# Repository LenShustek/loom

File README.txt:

eLoom: an automation system for the Glimakra "Julia" floor loom 

Tying up a loom with treadles and lamms is complicated, and so is the weaving. 
So I have replaced all the treadles and lamms in our Glimakra "Julia" 
countermarche floor loom with stepper motors that independently operate up to 
8 shafts. That not only makes setup and weaving easier, but it also allows 
patterns that would otherwise not be possible. 

The tie-ups and treadle sequences for up to 16 simulated treadles are 
graphically configured on a small screen. You then weave by throwing the 
shuttle and just pushing the single foot pedal to get the next configuration 
of the shafts. The warping, though, must still be done manually! 

For a one-minute video of it in action, see https://www.youtube.com/watch?v=ygZEDzQJMSk

The hardware added to the loom consists of:
 - up to 8 stepper motors, 23HS22-1504S, NEMA 23, 5.4V, 1.5A, 164 oz-in holding torque
 - up to 8 DRV8825 stepper motor drivers (Pololu or equiv.)
 - a 24VDC 200W power supply
 - 25-pitch sprockets and roller chain to connect the motors to the shaft lines
 - a control box that contains:
   - 1 4-row x 20-character LCD display (Adafruit 198)
   - 1 4-digit 7-segment I2C big digit numerical display (Adafruit 1268)
   - 2 rotary encoders with RGB LEDs and pushbuttons (Sparkfun COM-10982 and BOB-11722)
   - 4 general-purpose pushbuttons (MPJA 32730 or equiv.)
   - 1 attached foot pedal (MPJA 18150 or equiv.)
   - 1 Teensy 3.5 microprocessor, with 512KB flash, 192KB RAM, 4KB EEPROM, and 40 I/O pins
   
Len Shustek, January 2017

October 2020 update: After yeoman service for 3+ years, the plug-in breadboards with the
motor drivers started failing because the high current had deteriorated the contacts.
So I designed a proper printed circuit board replacement that is working great.
The design is in the motordriver subdirectory of this repository.

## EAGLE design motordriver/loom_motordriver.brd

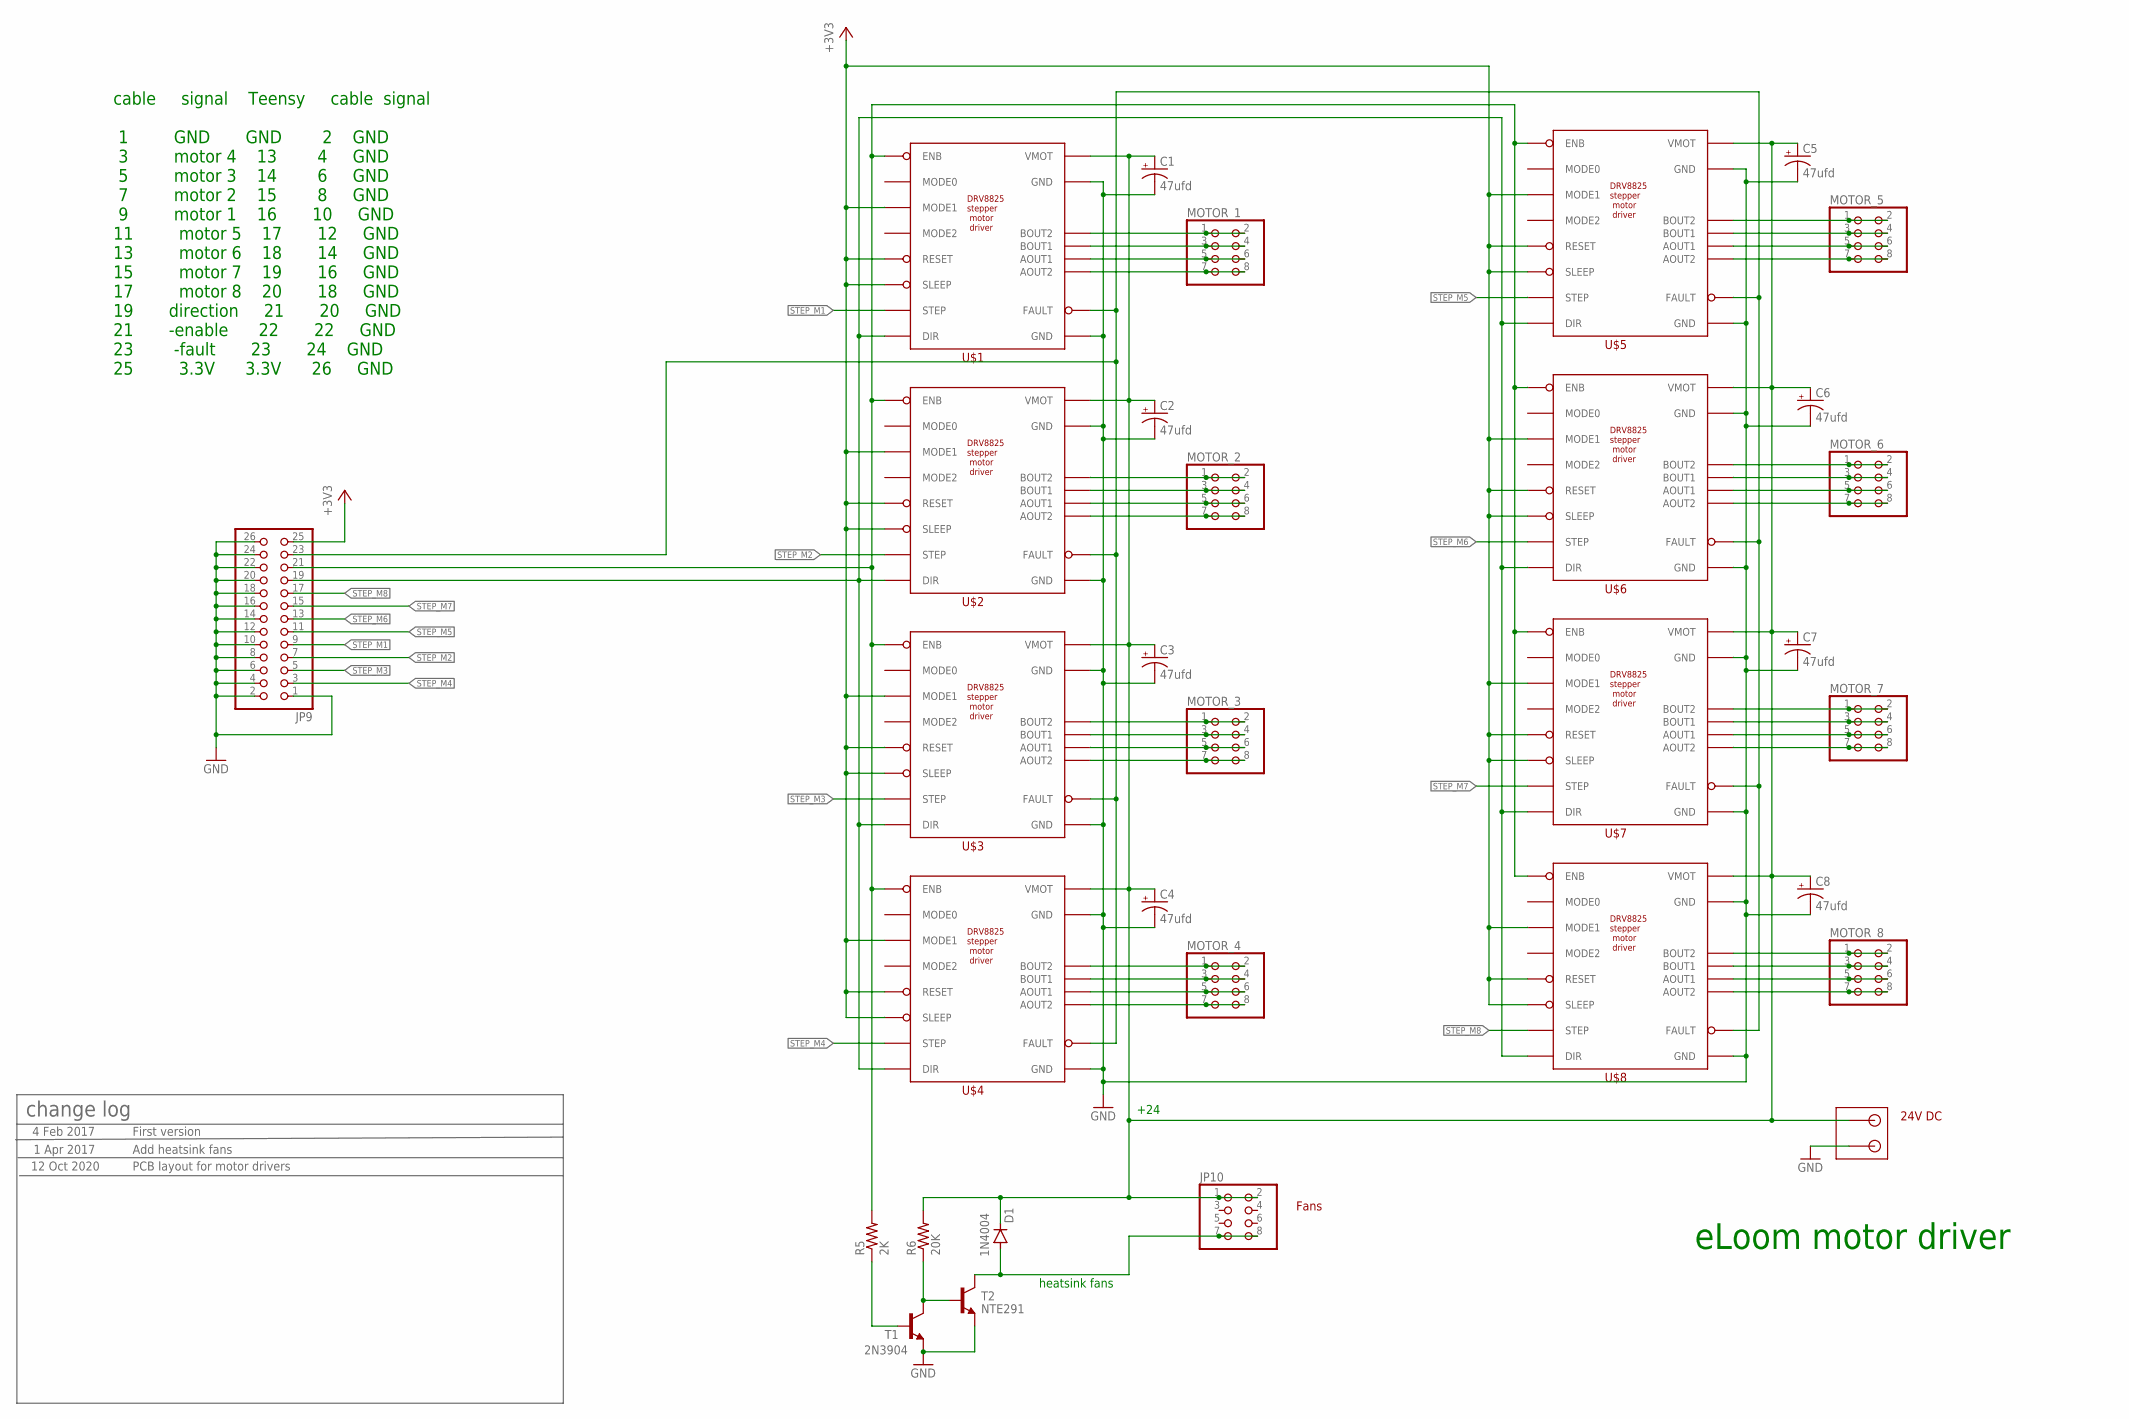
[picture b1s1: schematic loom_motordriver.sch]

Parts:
C1, C2, C3, C4, C5, C6, C7, C8: 47ufd; E2,5-6
D1: 1N4004; DO41-10
JP9: PINHD-2X13; 2X13
JP10: PINHD-2X4; 2X04
MOTOR_1, MOTOR_2, MOTOR_3, MOTOR_4, MOTOR_5, MOTOR_6, MOTOR_7, MOTOR_8: PINHD-2X4; 2X04
R5: 2K; 0204/7
R6: 20K; 0204/7
T1: 2N3904; TO92
T2: NTE291; TO220
U$1, U$2, U$3, U$4, U$5, U$6, U$7, U$8: DRV8825_STEPPER_MOTOR_DRIVER
U$9: CONNECTOR-2PIN; CONNECTOR-2PIN-5MM

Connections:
24V: C1.+, C2.+, C3.+, C4.+, C5.+, C6.+, C7.+, C8.+, D1.C, JP10.1, JP10.2, R6.2, U$1.P$16 (VMOT), U$2.P$16 (VMOT), U$3.P$16 (VMOT), U$4.P$16 (VMOT), U$5.P$16 (VMOT), U$6.P$16 (VMOT), U$7.P$16 (VMOT), U$8.P$16 (VMOT), U$9.P$1
+3V3: JP9.25, U$1.P$3 (MODE1), U$1.P$5 (RESET), U$1.P$6 (SLEEP), U$2.P$3 (MODE1), U$2.P$5 (RESET), U$2.P$6 (SLEEP), U$3.P$3 (MODE1), U$3.P$5 (RESET), U$3.P$6 (SLEEP), U$4.P$3 (MODE1), U$4.P$5 (RESET), U$4.P$6 (SLEEP), U$5.P$3 (MODE1), U$5.P$5 (RESET), U$5.P$6 (SLEEP), U$6.P$3 (MODE1), U$6.P$5 (RESET), U$6.P$6 (SLEEP), U$7.P$3 (MODE1), U$7.P$5 (RESET), U$7.P$6 (SLEEP), U$8.P$3 (MODE1), U$8.P$5 (RESET), U$8.P$6 (SLEEP)
DIR: JP9.19, U$1.P$8 (DIR), U$2.P$8 (DIR), U$3.P$8 (DIR), U$4.P$8 (DIR), U$5.P$8 (DIR), U$6.P$8 (DIR), U$7.P$8 (DIR), U$8.P$8 (DIR)
ENB: JP9.21, R5.2, U$1.P$1 (ENB), U$2.P$1 (ENB), U$3.P$1 (ENB), U$4.P$1 (ENB), U$5.P$1 (ENB), U$6.P$1 (ENB), U$7.P$1 (ENB), U$8.P$1 (ENB)
FAN: D1.A, JP10.7, JP10.8, T2.2 (C)
FAULT: JP9.23, U$1.P$10 (FAULT), U$2.P$10 (FAULT), U$3.P$10 (FAULT), U$4.P$10 (FAULT), U$5.P$10 (FAULT), U$6.P$10 (FAULT), U$7.P$10 (FAULT), U$8.P$10 (FAULT)
GND: C1.-, C2.-, C3.-, C4.-, C5.-, C6.-, C7.-, C8.-, JP9.1, JP9.2, JP9.4, JP9.6, JP9.8, JP9.10, JP9.12, JP9.14, JP9.16, JP9.18, JP9.20, JP9.22, JP9.24, JP9.26, T1.3 (E), T2.3 (E), U$1.P$9 (GND), U$1.P$15 (GND), U$2.P$9 (GND), U$2.P$15 (GND), U$3.P$9 (GND), U$3.P$15 (GND), U$4.P$9 (GND), U$4.P$15 (GND), U$5.P$9 (GND), U$5.P$15 (GND), U$6.P$9 (GND), U$6.P$15 (GND), U$7.P$9 (GND), U$7.P$15 (GND), U$8.P$9 (GND), U$8.P$15 (GND), U$9.P$2
unnamed: MOTOR_5.1, MOTOR_5.2, U$5.P$14 (BOUT2)
unnamed: MOTOR_5.3, MOTOR_5.4, U$5.P$13 (BOUT1)
unnamed: MOTOR_5.5, MOTOR_5.6, U$5.P$12 (AOUT1)
unnamed: MOTOR_5.7, MOTOR_5.8, U$5.P$11 (AOUT2)
unnamed: MOTOR_6.1, MOTOR_6.2, U$6.P$14 (BOUT2)
unnamed: MOTOR_6.3, MOTOR_6.4, U$6.P$13 (BOUT1)
unnamed: MOTOR_6.5, MOTOR_6.6, U$6.P$12 (AOUT1)
unnamed: MOTOR_6.7, MOTOR_6.8, U$6.P$11 (AOUT2)
unnamed: MOTOR_7.1, MOTOR_7.2, U$7.P$14 (BOUT2)
unnamed: MOTOR_7.3, MOTOR_7.4, U$7.P$13 (BOUT1)
unnamed: MOTOR_7.5, MOTOR_7.6, U$7.P$12 (AOUT1)
unnamed: MOTOR_7.7, MOTOR_7.8, U$7.P$11 (AOUT2)
unnamed: MOTOR_8.1, MOTOR_8.2, U$8.P$14 (BOUT2)
unnamed: MOTOR_8.3, MOTOR_8.4, U$8.P$13 (BOUT1)
unnamed: MOTOR_8.5, MOTOR_8.6, U$8.P$12 (AOUT1)
unnamed: MOTOR_8.7, MOTOR_8.8, U$8.P$11 (AOUT2)
unnamed: MOTOR_1.1, MOTOR_1.2, U$1.P$14 (BOUT2)
unnamed: MOTOR_1.3, MOTOR_1.4, U$1.P$13 (BOUT1)
unnamed: MOTOR_1.5, MOTOR_1.6, U$1.P$12 (AOUT1)
unnamed: MOTOR_1.7, MOTOR_1.8, U$1.P$11 (AOUT2)
unnamed: MOTOR_2.1, MOTOR_2.2, U$2.P$14 (BOUT2)
unnamed: MOTOR_2.3, MOTOR_2.4, U$2.P$13 (BOUT1)
unnamed: MOTOR_2.5, MOTOR_2.6, U$2.P$12 (AOUT1)
unnamed: MOTOR_2.7, MOTOR_2.8, U$2.P$11 (AOUT2)
unnamed: MOTOR_3.1, MOTOR_3.2, U$3.P$14 (BOUT2)
unnamed: MOTOR_3.3, MOTOR_3.4, U$3.P$13 (BOUT1)
unnamed: MOTOR_3.5, MOTOR_3.6, U$3.P$12 (AOUT1)
unnamed: MOTOR_3.7, MOTOR_3.8, U$3.P$11 (AOUT2)
unnamed: R5.1, T1.2 (B)
unnamed: R6.1, T1.1 (C), T2.1 (B)
unnamed: MOTOR_4.1, MOTOR_4.2, U$4.P$14 (BOUT2)
unnamed: MOTOR_4.3, MOTOR_4.4, U$4.P$13 (BOUT1)
unnamed: MOTOR_4.5, MOTOR_4.6, U$4.P$12 (AOUT1)
unnamed: MOTOR_4.7, MOTOR_4.8, U$4.P$11 (AOUT2)
STEP_M1: JP9.9, U$1.P$7 (STEP)
STEP_M2: JP9.7, U$2.P$7 (STEP)
STEP_M3: JP9.5, U$3.P$7 (STEP)
STEP_M4: JP9.3, U$4.P$7 (STEP)
STEP_M5: JP9.11, U$5.P$7 (STEP)
STEP_M6: JP9.13, U$6.P$7 (STEP)
STEP_M7: JP9.15, U$7.P$7 (STEP)
STEP_M8: JP9.17, U$8.P$7 (STEP)

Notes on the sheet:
eLoom motor driver
cable signal Teensy cable signal 1 GND GND 2 GND 3 motor 4 13 4 GND 5 motor 3 14 6 GND 7 motor 2 15 8 GND 9 motor 1 16 10 GND 11 motor 5 17 12 GND 13 motor 6 18 14 GND 15 motor 7 19 16 GND 17 motor 8 20 18 GND 19 direction 21 20 GND 21 -enable 22 22 GND 23 -fault 23 24 GND 25 3.3V 3.3V 26 GND
heatsink fans
+24
change log
4 Feb 2017
First version
1 Apr 2017
Add heatsink fans
24V DC
Fans
12 Oct 2020
PCB layout for motor drivers

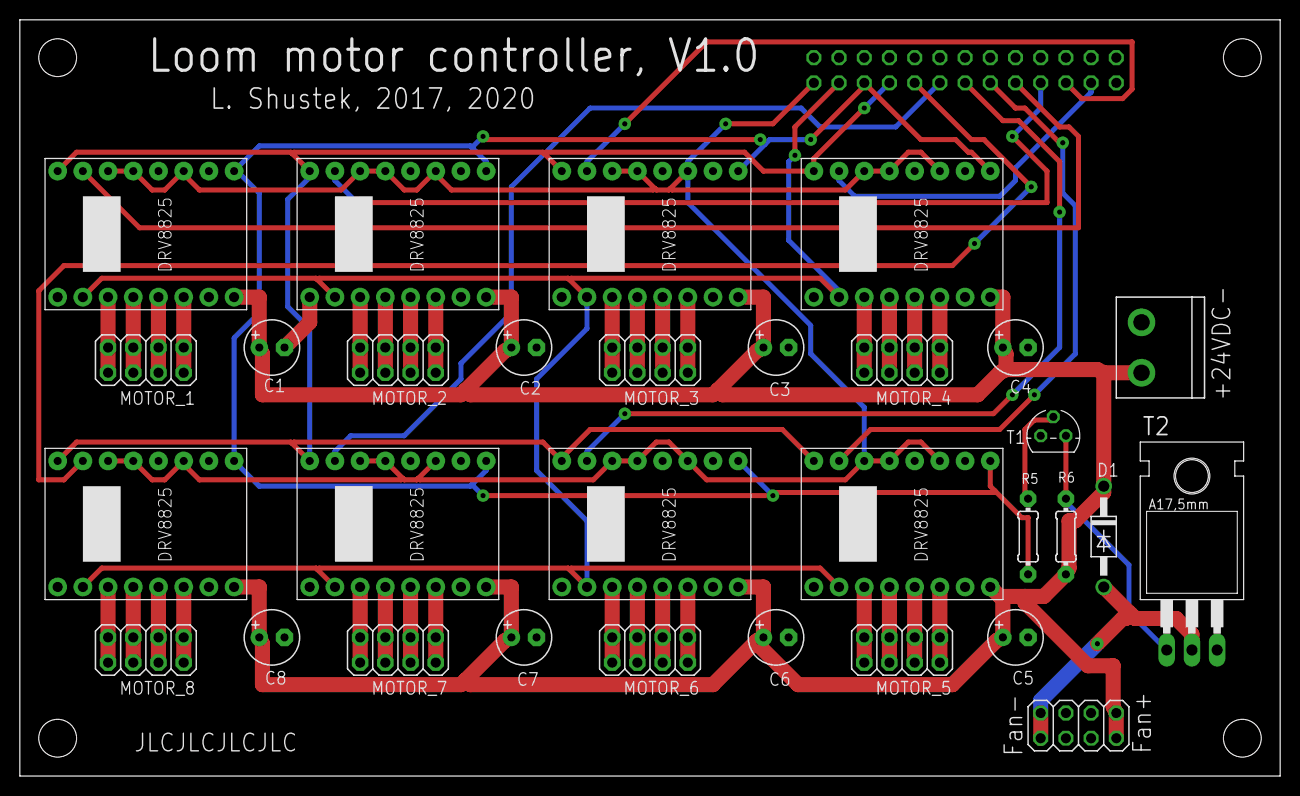
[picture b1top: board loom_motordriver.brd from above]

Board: 2 copper layers, 127.0 x 76.2 mm, 32 parts (1 on the bottom side), 49 nets.

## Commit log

2017-01-31 First version
2017-02-02 Minor tweaks to the first version
2017-02-09 small changes; see change log
2017-02-11 installed all 8 stepper motors
2017-02-12 add cable signal table
2017-02-14 added a link to the video of it in operation
2017-03-11 diagram the motorized countermarch actiion
2017-03-28 various small enhancements and bug fixes
2017-04-02 add circuit to switch heatsink fans on and off
2019-01-03 new features; bug fixes
2020-01-17 resize images to be visible in GitHub
2020-10-22 minor enhancements and bug fixes
2020-10-22 Made a printed circuit board for the motor drivers
